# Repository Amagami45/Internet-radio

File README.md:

# Internet-radio

This project is about building an internet radio receiver which will change the audio output to analog, which will be transferred to an old FM radio (AIWA). From the radio, audio will come out to connected speakers.

## Why?

I have an old Aiwa, which can do only FM and AM frequencies, and most radio stations start to turn to DAB+ signal. So that's the main reason why I chose building this internet radio receiver. Also, I can listen to foreign countries' radio stations.

## Technical specifications

It's powered by a USB-C 16-pin connector (5V). Then it's reduced to 3.3V by AMS1117 regulator. Most parts use 3.3V logic.

### Display
* 2.8" SPI TFT display (ILI9341 controller, 240x320). Connected via cables to the PCB.

### Buttons & Controls
I used Cherry MX switches and a rotary encoder:
* Reset button
* Sleep / ON button
* Up button
* Down button
* Rotary encoder – Volume up / Volume down
* Rotary encoder button – Sound off (Mute)

### Audio output
It's done by PCM5102A DAC chip (I2S audio interface) and 2 RCA cinches (Stereo Left/Right), which connect directly to AIWA AUX input.

## BOM (Bill of Materials)

* ESP32-WROOM-32 (with Bluetooth and Wi-Fi)
* PCM5102A DAC board/chip
* 2.8" SPI TFT Display (ILI9341)
* USB-C 16-pin connector (Type-C)
* AMS1117 3.3V LDO regulator
* Dual horizontal RCA cinch connector
* Cherry MX mechanical switches
* Rotary encoder
* 0603 SMD capacitors and resistors

## Schematics & PCB Design

I used KiCad for that (2-layer board design). Display will be connected by cables, that's why it is designed like it is. 

## 3D PCB & Case Renders

* 3D PCB export (.STEP) is generated from KiCad.
* All other parts and enclosure case are modeled in Fusion 360.

## 3D Printing Settings

* **Material:** PETG (recommended) or PLA
* **Layer Height:** 0.2 mm
* **Infill:** 15–20% (Gyroid or Grid)
* **Supports:** Needed only for RCA and USB-C cutouts on the rear panel

## Assembly Guide

### 1. PCB Assembly & Soldering
1. **SMD Components First:** Solder the small SMD parts first (AMS1117 regulator, 0603 capacitors/resistors, USB-C connector, and PCM5102A DAC).
2. **ESP32 Module:** Align and solder the ESP32-WROOM-32 module onto the board.
3. **Through-Hole Parts (THT):** Solder the Cherry MX switches, rotary encoder, and dual RCA cinch connector.

### 2. Display Wiring
* Connect the 2.8" ILI9341 TFT display to the PCB header using cables according to the KiCad schematic (VCC, GND, CS, RESET, DC, SDI/MOSI, SCK, LED).

### 3. Firmware Flashing
1. Connect the board to your PC via USB-C.
2. Flash **YoRadio** firmware using PlatformIO / Arduino IDE / Esptool.
3. Configure your GPIO pin mappings for the display, I2S DAC, rotary encoder, and Cherry MX buttons in `myoptions.h`.
4. Connect to the radio's Wi-Fi Access Point to set up your home Wi-Fi credentials and station playlist.

### 4. Enclosure Assembly
1. 3D print the case parts designed in Fusion 360.
2. Mount the 2.8" TFT display into the front panel slot.
3. Secure the PCB inside the main case using small M2/M3 screws.
4. Press keycaps onto the Cherry MX switches and attach the knob to the rotary encoder.
5. Close the 3D-printed enclosure.

### 5. Hooking up to AIWA
1. Connect an RCA stereo audio cable from the radio's cinch connectors to the **AUX / Line In** on your AIWA system.
2. Plug in a standard 5V USB-C power source.
3. Turn on AIWA, switch mode to AUX, select your favorite station, and enjoy!

# Pinout & Connections

## 1. ILI9341 Display (U4)
| ILI9341 Display | ESP32 (U1) / Power | Note |
| :--- | :--- | :--- |
| **VCC** | +3.3V | Logic / Display Power |
| **GND** | GND | Ground |
| **CS** | **IO0** (DISP_CS) | Display Chip Select |
| **D/C** | **IO16** (D/C) | Data / Command |
| **MOSI** | **IO23** | SPI MOSI |
| **MISO** | **IO19** | SPI MISO |
| **SCK** | **IO18** | SPI Clock |
| **LED** | **IO17** (LED) | Backlight Control |
| **RESET** | **RESET** (via D/C / RESET network) | Display Reset |

---

## 2. Micro SD Card Slot (J2)
| Micro SD Slot | Power Source / ESP32 (U1) | Note |
| :--- | :--- | :--- |
| **VDD (Pin 4)** | +3.3V | SD Card Power |
| **GND (Pin 3, 6)** | GND | Ground |
| **DAT3/CD (Pin 2)** | **IO12** (SD_CS) / **IO5** | Chip Select (10kΩ pull-up R6) |
| **CMD (Pin 3)** | **IO23** | SPI MOSI |
| **CLK (Pin 5)** | **IO18** | SPI SCK |
| **DAT0 (Pin 7)** | **IO19** | SPI MISO (10kΩ pull-up R16) |
| **DAT1 (Pin 8)** | — | 10kΩ pull-up R17 to +3.3V |
| **DAT2 (Pin 1)** | — | 10kΩ pull-up R15 to +3.3V |

---

## 3. Audio DAC PCM5102 (U3)
| PCM5102 Pin | ESP32 (U1) / Power | Function / Note |
| :--- | :--- | :--- |
| **CPVDD, DVDD, AVDD** | +3.3V | DAC Power (filtered by C3, C4, C5) |
| **GND, AGND, DGND** | GND | Ground |
| **LRCK (Pin 15)** | **IO25** | I2S Word Select (LRCK) |
| **DIN (Pin 14)** | **IO27** | I2S Data Input |
| **BCK (Pin 13)** | **IO26** | I2S Bit Clock |
| **SCK (Pin 12)** | GND | System Clock (connected to GND) |
| **OUTL (Pin 6)** | C3 / R5 / J3A Output | Left Channel Audio Output (Coaxial J3A) |
| **OUTR (Pin 7)** | C1 / R4 / J3B Output | Right Channel Audio Output (Coaxial J3B) |

---

## 4. Rotary Encoder with Button (SW1)
| Encoder Pin | ESP32 (U1) / Power | Note |
| :--- | :--- | :--- |
| **A (Pin A)** | **IO32** | Encoder Phase A |
| **B (Pin B)** | **IO33** | Encoder Phase B |
| **C (Pin C)** | GND | Encoder Common Pin |
| **S1 (Pin S1)** | **IO18** | Encoder Switch / Button |
| **S2 (Pin S2)** | GND | Encoder Switch Other Side |

---

## 5. Control Buttons
| Button | ESP32 Pin | Connection |
| :--- | :--- | :--- |
| **SW2** | **IO23** / **IO5** | Pushbutton to GND (switches to GND) |
| **SW3** | **IO22** | Pushbutton to GND (switches to GND) |
| **SW5** | **IO15** (via 1kΩ R12) | Pushbutton to GND (switches to GND) |
| **SW6** | **EN** | RESET button (switches EN to GND) |
| **SW7** | **IO3 (RXD)** (via R8/R11) | User / Boot Button |

---

## 6. USB-C UART Converter (CP2102N - U5) & Power Supply
* **USB Connector (J1):** Supplies VBUS (+5V) to the **AMS1117-3.3 (U2)** regulator, which generates the main **+3.3V** power supply for the entire circuit.
* **Converter CP2102N (U5):**
  * **TXD (Pin 21)** $\rightarrow$ **IO3 (RXD)** on ESP32 (via 1kΩ resistor R11)
  * **RXD (Pin 20)** $\leftarrow$ **IO1 (TXD)** from ESP32 (via 1kΩ resistor R12)
  * **DTR / RTS** $\rightarrow$ Connected to **Q1/Q2 (BC847)** transistors for automatic programming mode switching (EN and IO0).

## Software & Firmware

The radio firmware is built on the **ESP32** platform (Arduino IDE / PlatformIO) and ensures smooth reception of internet streams via Wi-Fi, their decoding, and digital audio processing.

### Key Features
* **Wi-Fi Connectivity:** Automatic connection to the configured network at system startup.
* **Audio Streaming (I2S):** Direct digital audio data transmission over the I2S interface to the PCM5102 DAC for high sound quality.
* **Station Management:** Pre-configured playlist of domestic and foreign radio stations (MP3/AAC streams) with sequential switching.
* **Volume Control:** Fine digital volume control directly inside the audio decoder.

### Control Mapping
Control is handled via buttons and a rotary encoder connected to the ESP32 GPIO pins:
* **SW3 (BTN_UP):** Switch to the next radio station.
* **SW2 (BTN_DOWN):** Switch to the previous radio station.
* **SW5 (BTN_LEFT):** Volume down.
* **SW7 (BTN_RIGHT):** Volume up.
* **SW1 (Encoder):** Menu navigation and additional features.

### Included Libraries
* **WiFi.h** – Network connection and wireless management.
* **ESP32-audioI2S** – Audio decoding and I2S communication handling.

## Credits & Acknowledgments

* Firmware powered by **ESP32-audioI2S** and **WiFi.h** library.

## License

This work is under GNU license. More info in LICENSE file.

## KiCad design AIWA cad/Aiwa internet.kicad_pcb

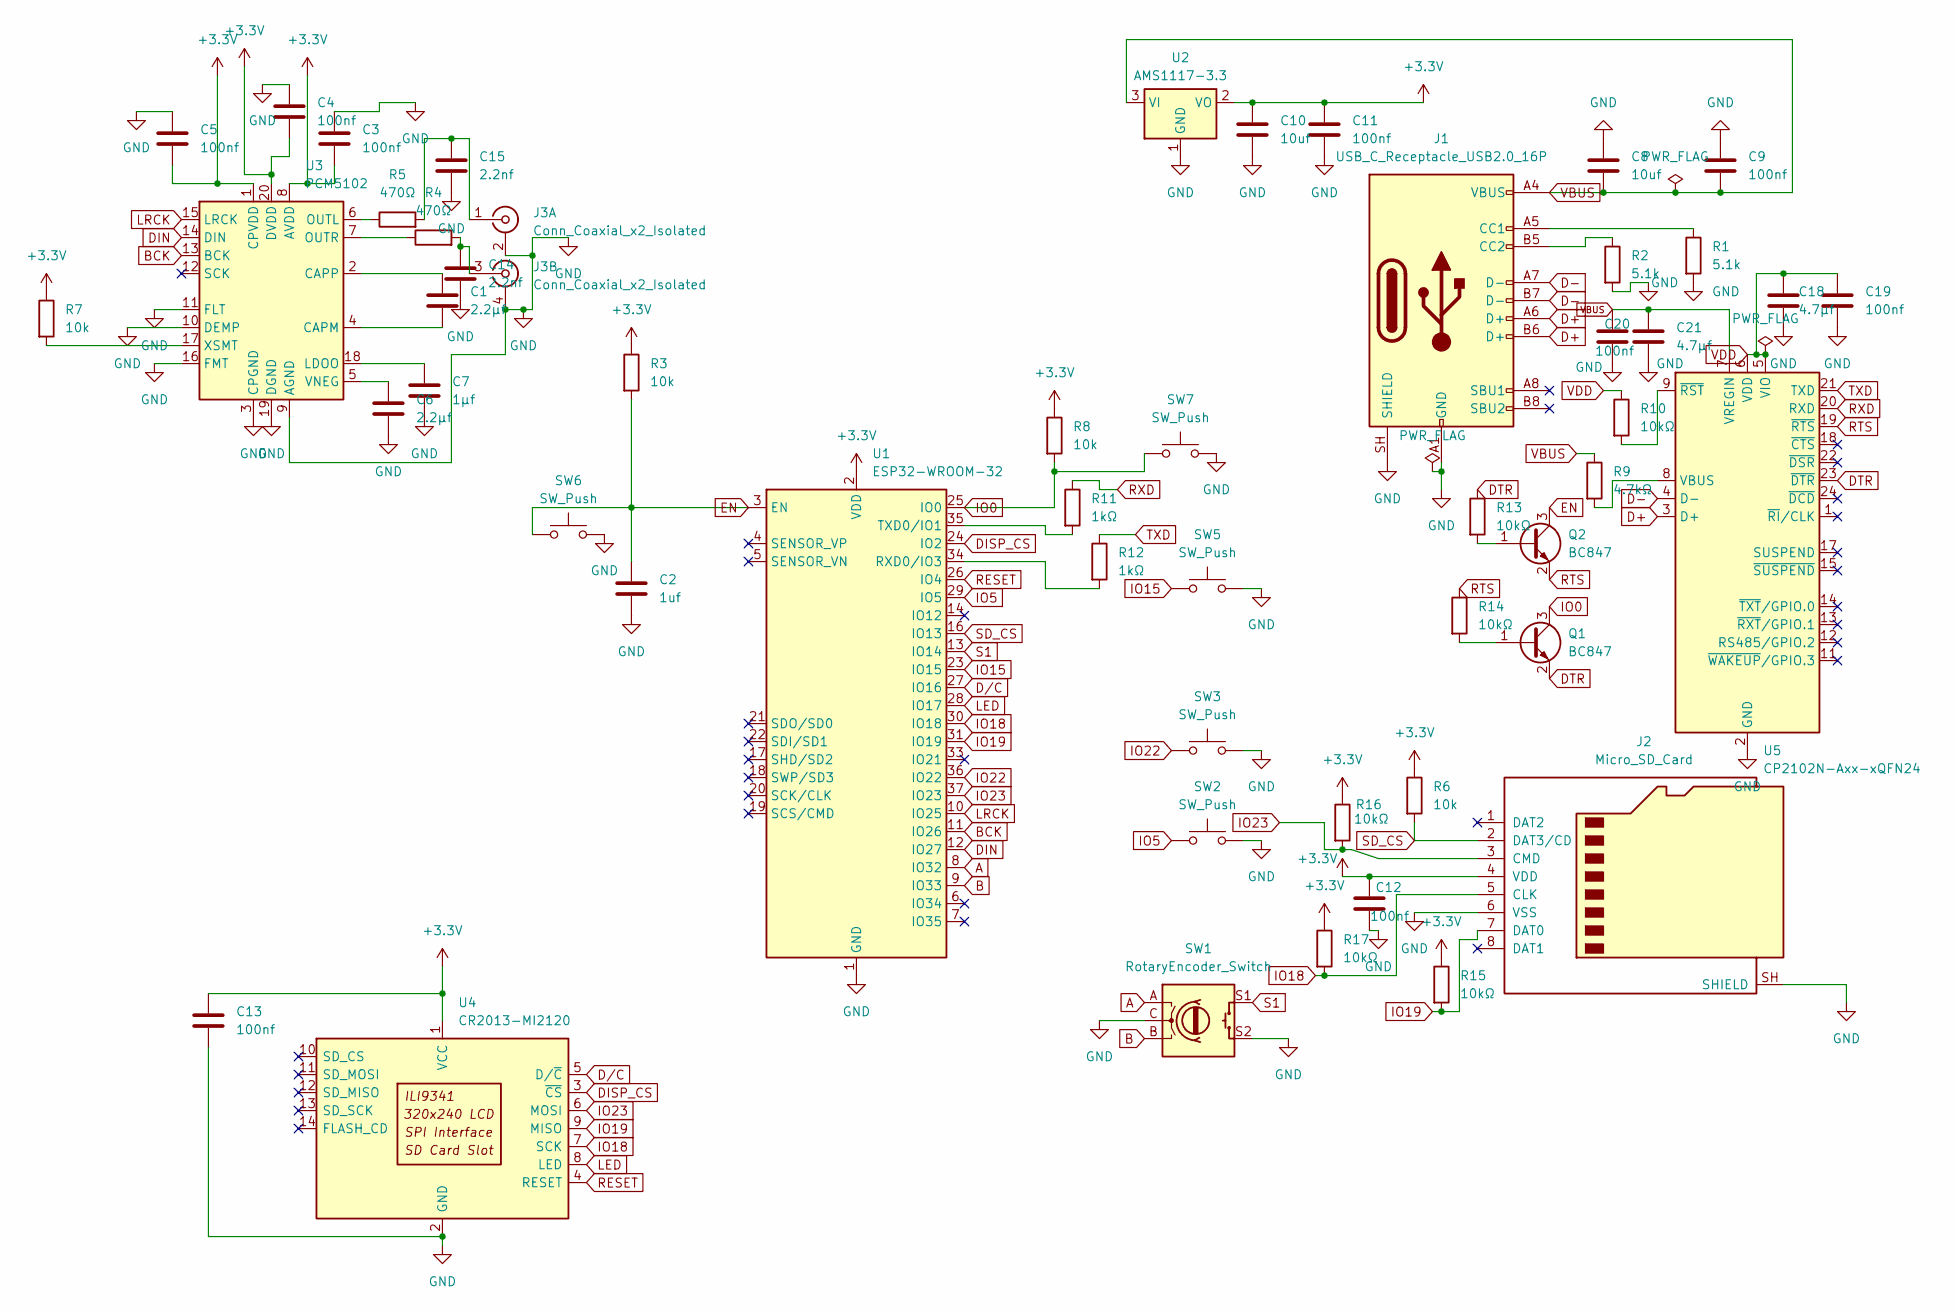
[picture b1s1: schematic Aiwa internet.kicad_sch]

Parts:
C1, C6: 2.2μf; C_0603_1608Metric
C2: 1uf; C_0603_1608Metric
C3, C4, C5, C9, C11, C12, C13, C19, C20: 100nf; C_0603_1608Metric
C7: 1μf; C_0603_1608Metric
C8, C10: 10uf; C_0603_1608Metric
C14, C15: 2.2nf; C_0603_1608Metric
C18, C21: 4.7µf; C_0603_1608Metric
J1: USB_C_Receptacle_USB2.0_16P; USB_C_Receptacle_HRO_TYPE-C-31-M-12
J2: Micro_SD_Card; microSD_HC_Hirose_DM3AT-SF-PEJM5
J3: Conn_Coaxial_x2_Isolated; PinHeader_1x04_P2.54mm_Vertical
Q1, Q2: BC847; SOT-23
R1, R2: 5.1k; R_0603_1608Metric
R3, R6, R7, R8: 10k; R_0603_1608Metric
R4, R5: 470Ω; R_0603_1608Metric
R9: 4.7kΩ; R_0603_1608Metric
R10, R13, R14, R15, R16, R17: 10kΩ; R_0603_1608Metric
R11, R12: 1kΩ; R_0603_1608Metric
SW1: RotaryEncoder_Switch; RotaryEncoder_Alps_EC11E-Switch_Vertical_H20mm
SW2, SW3, SW5, SW6, SW7: SW_Push; SW_Cherry_MX_1.00u_PCB
U1: ESP32-WROOM-32
U2: AMS1117-3.3; SOT-223-3_TabPin2
U3: PCM5102; TSSOP-20_4.4x6.5mm_P0.65mm
U4: CR2013-MI2120
U5: CP2102N-Axx-xQFN24; QFN-24-1EP_4x4mm_P0.5mm_EP2.6x2.6mm

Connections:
+3.3V: C3.2, C4.2, C5.2, C10.1, C11.1, C12.1, C13.1, J2.4 (VDD), R3.1, R6.1, R7.1, R8.1, R15.1, R16.1, R17.1, U1.2 (VDD), U2.2 (VO), U3.1 (CPVDD), U3.8 (AVDD), U3.20 (DVDD), U4.1 (VCC)
A: SW1.A, U1.8 (IO32)
B: SW1.B, U1.9 (IO33)
BCK: U1.11 (IO26), U3.13 (BCK)
D+: J1.A6 (D+), J1.B6 (D+), U5.3 (D+)
D-: J1.A7 (D-), J1.B7 (D-), U5.4 (D-)
DIN: U1.12 (IO27), U3.14 (DIN)
DISP_CS: U1.24 (IO2), U4.3 (~CS)
DTR: Q1.2 (E), R13.1, U5.23 (~DTR)
D/C: U1.27 (IO16), U4.5 (D/~C)
EN: C2.1, Q2.3 (C), R3.2, SW6.1, U1.3 (EN)
GND: C2.2, C3.1, C4.1, C5.1, C6.2, C7.2, C8.1, C9.1, C10.2, C11.2, C12.2, C13.2, C14.2, C15.2, C18.2, C19.2, C20.2, C21.2, J1.A1 (GND), J1.A12 (GND), J1.B1 (GND), J1.B12 (GND), J1.SH (SHIELD), J2.6 (VSS), J2.SH (SHIELD), J3.2 (Ext1), J3.4 (Ext2), R1.2, R2.2, SW1.C, SW1.S2, SW2.2, SW3.2, SW5.2, SW6.2, SW7.2, U1.1 (GND), U1.15 (GND), U1.38 (GND), U1.39 (GND), U2.1 (GND), U3.3 (CPGND), U3.9 (AGND), U3.10 (DEMP), U3.11 (FLT), U3.16 (FMT), U3.19 (DGND), U4.2 (GND), U5.2 (GND), U5.25 (GND)
IO0: Q1.3 (C), R8.2, SW7.1, U1.25 (IO0)
IO5: SW2.1, U1.29 (IO5)
IO15: SW5.1, U1.23 (IO15)
IO18: J2.5 (CLK), R17.2, U1.30 (IO18), U4.7 (SCK)
IO19: J2.7 (DAT0), R15.2, U1.31 (IO19), U4.9 (MISO)
IO22: SW3.1, U1.36 (IO22)
IO23: J2.3 (CMD), R16.2, U1.37 (IO23), U4.6 (MOSI)
LED: U1.28 (IO17), U4.8 (LED)
LRCK: U1.10 (IO25), U3.15 (LRCK)
unnamed: J1.A5 (CC1), R1.1
unnamed: J1.B5 (CC2), R2.1
unnamed: C15.1, J3.1 (In1), R5.2
unnamed: C14.1, J3.3 (In2), R4.2
unnamed: Q1.1 (B), R14.2
unnamed: Q2.1 (B), R13.2
unnamed: R12.2, U1.34 (RXD0/IO3)
unnamed: R11.2, U1.35 (TXD0/IO1)
unnamed: C1.2, U3.4 (CAPM)
unnamed: C1.1, U3.2 (CAPP)
unnamed: C7.1, U3.18 (LDOO)
unnamed: R5.1, U3.6 (OUTL)
unnamed: R4.1, U3.7 (OUTR)
unnamed: C6.1, U3.5 (VNEG)
unnamed: R7.2, U3.17 (XSMT)
unnamed: R9.2, U5.8 (VBUS)
unnamed: R10.2, U5.9 (~RST)
RESET: U1.26 (IO4), U4.4 (RESET)
RTS: Q2.2 (E), R14.1, U5.19 (~RTS)
RXD: R11.1, U5.20 (RXD)
S1: SW1.S1, U1.13 (IO14)
SD_CS: J2.2 (DAT3/CD), R6.2, U1.16 (IO13)
TXD: R12.1, U5.21 (TXD)
VBUS: C8.2, C9.2, C20.1, C21.1, J1.A4 (VBUS), J1.A9 (VBUS), J1.B4 (VBUS), J1.B9 (VBUS), R9.1, U2.3 (VI), U5.7 (VREGIN)
VDD: C18.1, C19.1, R10.1, U5.5 (VIO), U5.6 (VDD)

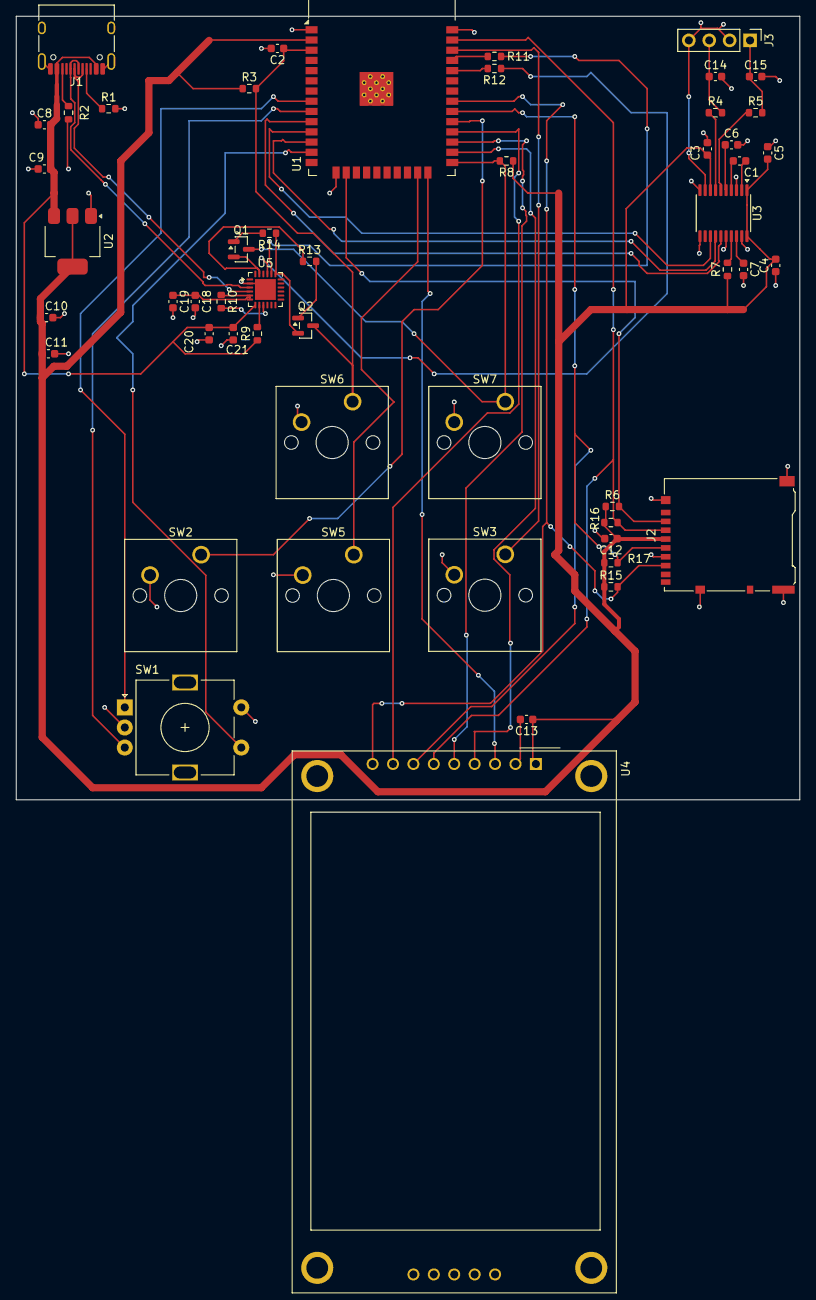
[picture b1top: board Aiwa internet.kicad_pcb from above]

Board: 2 copper layers, 97.5 x 97.5 mm, 52 parts (0 on the bottom side), 46 nets.

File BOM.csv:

No,Quantity,Comment,Designator,Footprint,Value,Manufacturer Part,Manufacturer,Supplier Part,Supplier,Price,URL
1,1,ESP32 Wi-Fi/BT Module,U1,RF_Module:ESP32-WROOM-32,ESP32-WROOM-32,ESP32-WROOM-32E-N4,Espressif,C473012,LCSC,2.85$,https://www.lcsc.com/product-detail/WiFi-Modules_Espressif-S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
2,1,3.3V LDO Voltage Regulator,U2,Package_TO_SOT_SMD:SOT-223-3_TabPin2,AMS1117-3.3,AMS1117-3.3,AMS,C6186,LCSC,0.12$,https://www.lcsc.com/product-detail/Linear-Voltage-Regulator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
3,1,I2S Audio DAC Chip,U3,Package_SO:TSSOP-20_4.4x6.5mm_P0.65mm,PCM5102A,PCM5102AIPWR,Texas Instruments,C67139,LCSC,1.80$,https://www.lcsc.com/product-detail/Audio-Processors-DACS-MD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
4,1,TFT Display Screen,U4,Display:CR2013-MI2120,CR2013-MI2120,CR2013-MI2120,Generic,Custom,AliExpress,2.50$,http://pan.baidu.com/s/11Y990
5,1,USB-to-UART Bridge,U5,Package_DFN_QFN:QFN-24-1EP_4x4mm_P0.5mm_EP2.6x2.6mm,CP2102N-Axx-xQFN24,CP2102N-A02-GQFN24R,Silicon Labs,C141118,LCSC,1.20$,https://www.lcsc.com/product-detail/USB-IC_Silicon-Labs-CP21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
6,2,NPN Transistor,"Q1, Q2",Package_TO_SOT_SMD:SOT-23,BC847,BC847B,Nexperia,C2131,LCSC,0.02$,https://www.lcsc.com/product-detail/Bipolar-Transistors-BJT_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
7,1,USB-C Receptacle 16P,J1,Connector_USB:USB_C_Receptacle_HRO_TYPE-C-31-M-12,TYPE-C 16PIN 2MD(073),TYPE-C 16PIN 2MD(073),SHOU HAN,C2765186,LCSC,0.08$,https://www.lcsc.com/product-detail/C2765186.html
8,1,Micro SD Card Slot,J2,Connector_Card:microSD_HC_Hirose_DM3AT-SF-PEJM5,Micro_SD_Card,DM3AT-SF-PEJM5,Hirose,C114219,LCSC,0.40$,https://www.we-online.com/components/products/datasheet/6930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
9,1,4-Pin Header (Audio Out),J3,Connector_PinHeader_2.54mm:PinHeader_1x04_P2.54mm_Vertical,Conn_Coaxial_x2_Isolated,Header-1x4P-2.54,Generic,C22548,LCSC,0.05$,https://www.lcsc.com/product-detail/Pin-Header-Female-Header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
10,1,Rotary Encoder with Switch,SW1,Rotary_Encoder:RotaryEncoder_Alps_EC11E-Switch_Vertical_H20mm,RotaryEncoder_Switch,EC11E1224404,ALPS,C25243,LCSC,0.50$,https://www.lcsc.com/product-detail/Encoders_ALPS-EC11E12244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
11,5,Cherry MX Push Switch,"SW2, SW3, SW5, SW6, SW7",Button_Switch_Keyboard:SW_Cherry_MX_1.00u_PCB,SW_Push,MX-1.0U,Cherry,Custom,AliExpress,0.25$,https://www.aliexpress.com
12,2,5.1k Resistor 0603,"R1, R2",Resistor_SMD:R_0603_1608Metric,5.1k,0603WAF5101T5E,UNI-ROYAL,C23186,LCSC,0.005$,https://www.lcsc.com/product-detail/C23186.html
13,10,10k Resistor 0603,"R3, R6, R7, R8, R10, R13, R14, R15, R16, R17",Resistor_SMD:R_0603_1608Metric,10k,0603WAF1002T5E,UNI-ROYAL,C25804,LCSC,0.005$,https://www.lcsc.com/product-detail/Chip-Resistor-Surface-Mo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
14,2,470R Resistor 0603,"R4, R5",Resistor_SMD:R_0603_1608Metric,470R,0603WAF4700T5E,UNI-ROYAL,C23179,LCSC,0.005$,https://www.lcsc.com/product-detail/Chip-Resistor-Surface-Mo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
15,1,4.7k Resistor 0603,R9,Resistor_SMD:R_0603_1608Metric,4.7k,0603WAF4701T5E,UNI-ROYAL,C23162,LCSC,0.005$,https://www.lcsc.com/product-detail/Chip-Resistor-Surface-Mo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
16,2,1k Resistor 0603,"R11, R12",Resistor_SMD:R_0603_1608Metric,1k,0603WAF1001T5E,UNI-ROYAL,C21190,LCSC,0.005$,https://www.lcsc.com/product-detail/Chip-Resistor-Surface-Mo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
17,2,2.2uF Capacitor 0603,"C1, C6",Capacitor_SMD:C_0603_1608Metric,2.2uF,CL10A225KP8NNNC,SAMSUNG,C15858,LCSC,0.01$,https://www.lcsc.com/product-detail/Multilayer-Ceramic-Capac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
18,2,1uF Capacitor 0603,"C2, C7",Capacitor_SMD:C_0603_1608Metric,1uF,CL10A105KB8NNNC,SAMSUNG,C15849,LCSC,0.01$,https://www.lcsc.com/product-detail/C15849.html
19,9,100nF Capacitor 0603,"C3, C4, C5, C9, C11, C12, C13, C19, C20",Capacitor_SMD:C_0603_1608Metric,100nF,CL10B104KB8NNNC,SAMSUNG,C14663,LCSC,0.005$,https://www.lcsc.com/product-detail/Multilayer-Ceramic-Capac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
20,2,10uF Capacitor 0603,"C8, C10",Capacitor_SMD:C_0603_1608Metric,10uF,CL10A106MO8NNNC,SAMSUNG,C19702,LCSC,0.02$,https://www.lcsc.com/product-detail/Multilayer-Ceramic-Capac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
21,2,2.2nF Capacitor 0603,"C14, C15",Capacitor_SMD:C_0603_1608Metric,2.2nF,CL10B222KB8NNNC,SAMSUNG,C1600,LCSC,0.005$,https://www.lcsc.com/product-detail/Multilayer-Ceramic-Capac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
22,2,4.7uF Capacitor 0603,"C18, C21",Capacitor_SMD:C_0603_1608Metric,4.7uF,CL10A475KP8NNNC,SAMSUNG,C19666,LCSC,0.01$,https://www.lcsc.com/product-detail/Multilayer-Ceramic-Capac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
